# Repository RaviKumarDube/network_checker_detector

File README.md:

# network_checker_detector

A hardware-based **Sequential Network Cable Tester** designed in KiCad. This tool detects signal frequency and pin-to-pin continuity for RJ45 Ethernet cables.

##  Project Description
This device identifies wiring faults in network cables by cycling a signal through all 8 pins sequentially. It uses hardware logic (no MCU required) to provide real-time visual feedback via an LED array.

### Features
*   **Sequential Testing:** Automatically cycles through pins 1-8.
*   **Hardware Logic:** Uses a 555-Timer and 4017-Counter architecture.
*   **Visual Debugging:** 10-LED indicator row for signal tracking.
*   **Low Power:** Designed for standard DC input or 9V battery operation.

---

##  Hardware Architecture

### Logic Flow
1. **Clock Generation (U1):** An **NE555 Timer** generates a square wave (the system heartbeat).
2. **Signal Sequencing (U3):** A **CD4017 Decade Counter** receives the clock and shifts a "High" signal across pins 0-7.
3. **Transmission (J1/J3):** The signal is sent through the RJ45 connectors.
4. **Visual Output:** If the physical wire is intact, the corresponding LED (D2-D19) illuminates.

### Key Components

| Ref | Component | Description |
| :--- | :--- | :--- |
| **U1** | NE555 | Astable Multivibrator (Clock) |
| **U3** | CD4017 | Decade Counter (Sequencer) |
| **D2-D19** | 1N4148 | Signal Diodes (Backflow Protection) |
| **J1, J3** | RJ45 | Ethernet Testing Ports |

---

##  Repository Structure
```text
├── hardware/
│   ├── networkdetector.kicad_sch  
│   ├── networkdetector.kicad_pcb  
│   └── networkdetector.kicad_pro  
├── renders/
│   └── 3d_view.png               
└── docs/
    └── BOM.csv
```

## Images

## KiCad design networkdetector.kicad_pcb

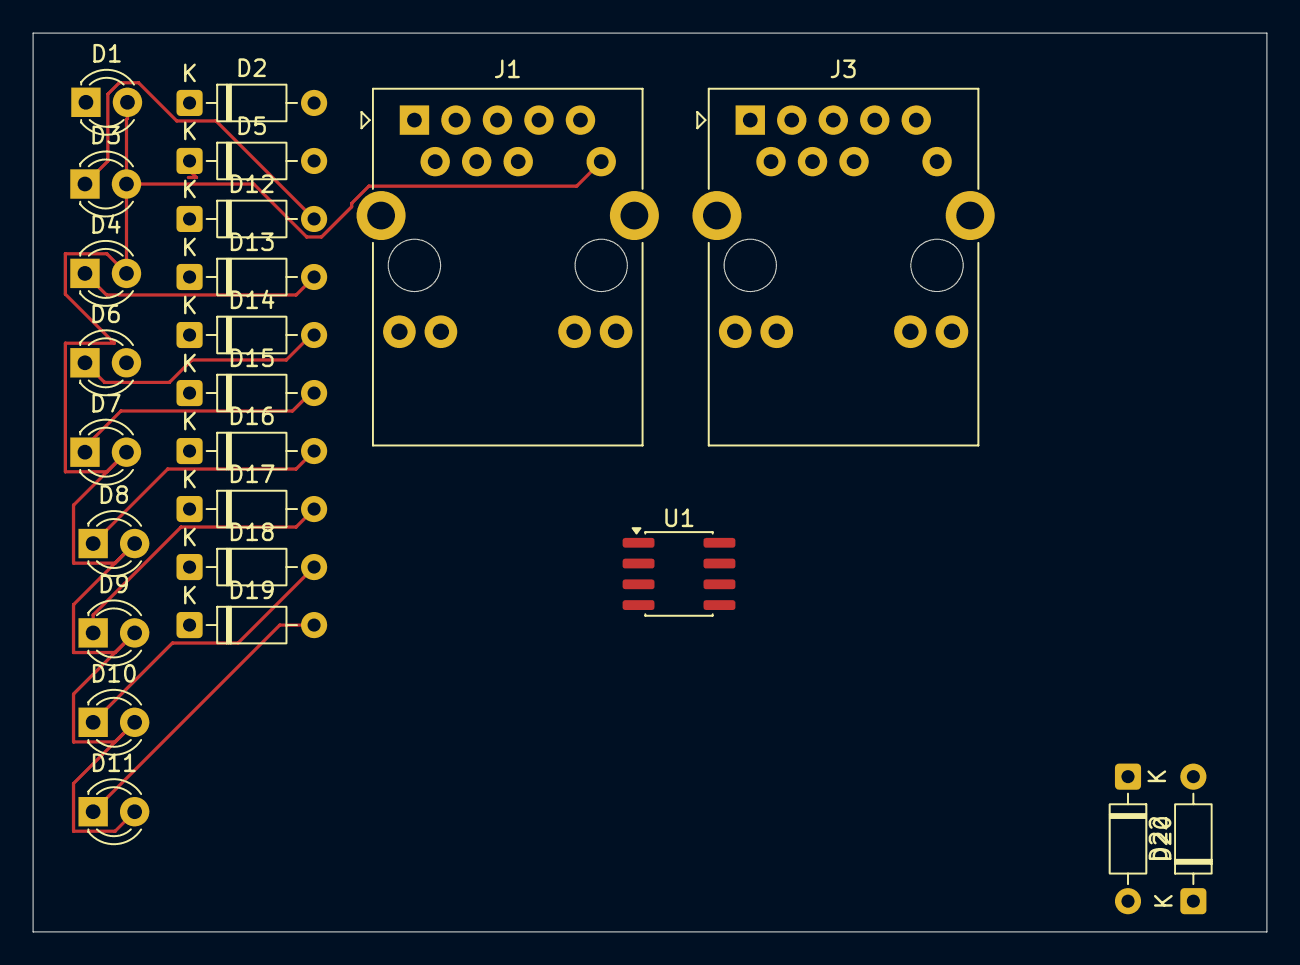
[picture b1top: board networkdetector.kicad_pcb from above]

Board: 2 copper layers, 75.5 x 55.0 mm, 24 parts (0 on the bottom side), 9 nets.

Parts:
D1: LED; LED_D3.0mm
D2, D5, D12, D13, D14, D15, D16, D17, D18, D19, D20, D22: 1N4148; D_DO-35_SOD27_P7.62mm_Horizontal
D3, D4, D6, D7, D8, D9, D10, D11: RED; LED_D3.0mm
J1, J3: RJ45_Abracon_ARJP11A-MASA-B-A-EMU2; RJ45_Abracon_ARJP11A-MA_Horizontal
U1: NE555D; SOIC-8_3.9x4.9mm_P1.27mm

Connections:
/GND: D1.2 (A_2), D3.2 (A), D4.2 (A), D6.2 (A), D7.2 (A), D8.2 (A), D9.2 (A), D10.2 (A), D11.2 (A), J1.10 (V-_10)
unnamed: D10.1 (K), D18.2 (A)
unnamed: D11.1 (K), D19.2 (A)
unnamed: D3.1 (K), D12.2 (A)
unnamed: D4.1 (K), D13.2 (A)
unnamed: D6.1 (K), D14.2 (A)
unnamed: D7.1 (K), D15.2 (A)
unnamed: D8.1 (K), D16.2 (A)
unnamed: D9.1 (K), D17.2 (A)

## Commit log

2026-04-19 Enhance README with project details and structure
    Added detailed project description, features, hardware architecture, key components, and repository structure to README.
2026-04-19 Add image section to README
    Added an image section to the README with a PCB image.
